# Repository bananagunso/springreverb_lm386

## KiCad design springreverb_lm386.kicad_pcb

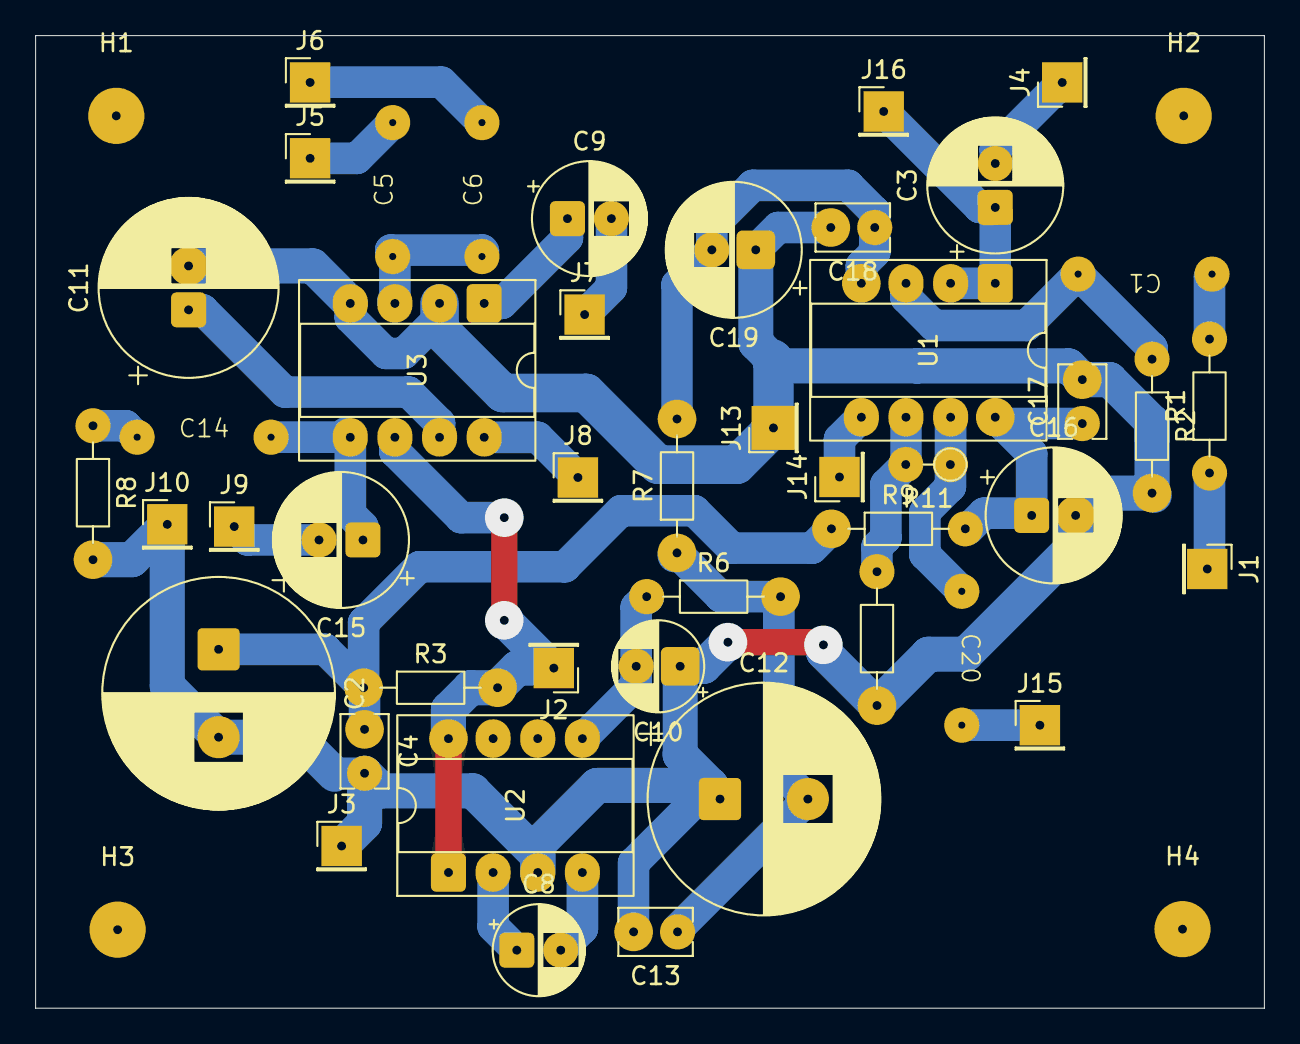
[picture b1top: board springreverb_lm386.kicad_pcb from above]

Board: 2 copper layers, 69.9 x 55.3 mm, 49 parts (0 on the bottom side), 28 nets.

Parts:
C1: 0.1u; 9.3_4.3_p7.5
C2, C12: 1000u; CP_Radial_D13.0mm_P5.00mm
C3, C15, C16, C19: 100u; CP_Radial_D7.5mm_P2.50mm
C4, C13, C17, C18: 0.1u; C_Rect_L4.0mm_W2.5mm_P2.50mm
C5: 4700p; 9.3_4.3_p7.5
C6: 470p; 9.3_4.3_p7.5
C8, C10: 10u; CP_Radial_D5.0mm_P2.50mm
C9: 10u; CP_Radial_D6.3mm_P2.50mm
C11: 100u; CP_Radial_D10.0mm_P2.50mm
C14: 0.047u; 9.3_4.3_p7.5
C20: 0.022uF; 9.3_4.3_p7.5
H1, H2, H3, H4: MountingHole; MountingHole_3.2mm_M3
J1: IN; PinHeader_1x01_P2.54mm_Vertical
J2: Vin; PinHeader_1x01_P2.54mm_Vertical
J3: GND; PinHeader_1x01_P2.54mm_Vertical
J4: VR1_3; PinHeader_1x01_P2.54mm_Vertical
J5: toC6; PinHeader_1x01_P2.54mm_Vertical
J6: toC7; PinHeader_1x01_P2.54mm_Vertical
J7: VR2_3; PinHeader_1x01_P2.54mm_Vertical
J8: VR_2_2; PinHeader_1x01_P2.54mm_Vertical
J9: To; PinHeader_1x01_P2.54mm_Vertical
J10: FromSW; PinHeader_1x01_P2.54mm_Vertical
J13: FromGND; PinHeader_1x01_P2.54mm_Vertical
J14: From; PinHeader_1x01_P2.54mm_Vertical
J15: VR_3_1; PinHeader_1x01_P2.54mm_Vertical
J16: VR4_1; PinHeader_1x01_P2.54mm_Vertical
R1: 10k; R_Axial_DIN0204_L3.6mm_D1.6mm_P7.62mm_Horizontal
R2: 1M; R_Axial_DIN0204_L3.6mm_D1.6mm_P7.62mm_Horizontal
R3, R6, R8: 10; R_Axial_DIN0204_L3.6mm_D1.6mm_P7.62mm_Horizontal
R7, R9: 470; R_Axial_DIN0204_L3.6mm_D1.6mm_P7.62mm_Horizontal
R10: 2.2k; R_Axial_DIN0204_L3.6mm_D1.6mm_P7.62mm_Horizontal
R11: 220k; R_Axial_DIN0204_L3.6mm_D1.6mm_P2.54mm_Vertical
U1: TL072; CERDIP-8_W7.62mm_SideBrazed_Socket
U2: TC1044S; CERDIP-8_W7.62mm_SideBrazed_Socket
U3: LM386; CERDIP-8_W7.62mm_SideBrazed_Socket

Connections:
GND: C2.2, C4.2, C10.1, C11.2, C12.1, C13.2, C16.2, C17.2, C18.2, C19.1, J3.1 (Pin_1_1), J10.1 (Pin_1_1), J13.1 (Pin_1_1), R2.2, R8.2, R10.2, U2.3 (GND), U3.2 (-), U3.4 (GND)
unnamed: C1.1, R1.2
unnamed: C2.1, C4.1, R3.1, R9.1
unnamed: C9.1, U3.1 (GAIN)
unnamed: C12.2, C13.1, R6.2, R7.1
unnamed: C14.1, R8.1
unnamed: C14.2, C15.1, U3.5
unnamed: C20.1, R11.1, U1.7
unnamed: J1.1 (Pin_1_1), R1.1
unnamed: J2.1 (Pin_1_1), R3.2, U2.1 (BOOST), U2.8 (V+), U3.6 (V+)
unnamed: C3.2, J4.1 (Pin_1_1)
unnamed: C5.2, J5.1 (Pin_1_1)
unnamed: C6.2, J6.1 (Pin_1_1)
unnamed: C9.2, J7.1 (Pin_1_1)
unnamed: J8.1 (Pin_1_1), U3.8 (GAIN)
unnamed: C15.2, J9.1 (Pin_1_1)
unnamed: J14.1 (Pin_1_1), U1.5 (+)
unnamed: C20.2, J15.1 (Pin_1_1)
unnamed: C3.1, J16.1 (Pin_1_1), U1.1, U1.2 (-)
unnamed: C1.2, R2.1, U1.3 (+)
unnamed: R10.1, R11.2, U1.6 (-)
unnamed: C16.1, C17.1, R9.2, U1.8 (V+)
unnamed: C18.1, C19.2, R7.2, U1.4 (V-)
unnamed: C8.1, U2.2 (CAP+)
unnamed: C8.2, U2.4 (CAP-)
unnamed: C10.2, R6.1, U2.5 (VOUT)
unnamed: C5.1, C6.1, U3.3 (+)
unnamed: C11.1, U3.7 (BYPASS)

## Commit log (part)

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2026-04-28 トーン回路修正
2026-04-30 フィルムコンデンサを変更
2026-05-01 フットプリント修正
